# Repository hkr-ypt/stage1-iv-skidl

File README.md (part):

# Stage 1 I–V Characterization System — SKiDL Project

A complete, **executable** [SKiDL](https://github.com/devbisme/skidl) source
design for a Stage 1 I–V characterization instrument: a precision bipolar
**±10 V** voltage-source with 4-wire **Kelvin** sensing, **bipolar voltage and
current measurement over the whole sweep** (±11.8 V, ±97.8 mA guaranteed at the
nominal channel gain; ±11.76 V, ±97.3 mA with gain and offset at their limits; for a
source that can reach ±10.04 V and ±91.3 mA), hardware current limiting
(~49 mA), defense-in-depth protection, and a **shared 2.500 V reference** for
ratiometric measurement.

This project is the source of truth for the electrical design **and** the
board. Running it produces a **KiCad netlist** (`stage1_iv.net`), a
**hierarchical KiCad schematic** (`stage1_iv.kicad_sch` + one child
`.kicad_sch` per block, generated from the same in-memory circuit — see
[`SCHEMATIC.md`](SCHEMATIC.md)), the **placed and fully routed bipolar board**
(`stage1_iv.kicad_pcb`), plus a generated component manifest.

> **The board is generated from source and fully routed.** Its placement and
> copper are the human-routed board's (`unipolar-routed/`), captured into
> [`layout/stage1_iv.layout`](layout/stage1_iv.layout); the bipolar
> measurement change is applied to it by
> [`layout/bipolar.eco`](layout/bipolar.eco), the final hardware audit
> corrections by [`layout/audit_corrections.eco`](layout/audit_corrections.eco),
> the remaining corrections (FORCE+ photorelay, dead-rail clamps, FORCE−
> PTC, R10, F1 placement, mounting holes) by
> [`layout/final_corrections.eco`](layout/final_corrections.eco), and the
> re-routing to the repository clearances by
> [`layout/policy_clearance.eco`](layout/policy_clearance.eco): lists of
> add/remove operations, each with its reason. See
> [`docs/physical_design.md`](docs/physical_design.md),
> [`docs/audit_corrections.md`](docs/audit_corrections.md) and
> [`docs/final_corrections.md`](docs/final_corrections.md).
>
> **KiCad 10 DRC** (zones refilled, schematic parity on): 0 unconnected, 0
> parity problems, and **0 errors** both under the rules the board was routed
> to (its 0.20 mm netclass plus the scoped intra-footprint rules, every check
> on) and under the repository's stricter netclass policy (0.25–0.30 mm
> around sense and ±15 V nets). Two silkscreen-to-edge warnings at J3 are
> also on the original.
>
> **`unipolar-routed/` is the original, unipolar, human-routed reference** and is never
> modified. `python3 tools/reproduce_reference.py` proves the layout source
> regenerates it (identical copper, placement and connectivity; identical
> KiCad DRC and zone fill).

---

## Where the pin numbers come from

Every component is a **SKiDL-native part** (`tool=SKIDL`) declared in
[`libraries/custom_symbols.py`](libraries/custom_symbols.py), so the design runs
ERC, builds the netlist and validates connectivity as plain Python. But the
pins are **not written there**: each factory names an official KiCad `lib_id`,
and the pin numbers, pin names and electrical types are *read out of the
installed KiCad symbol library at build time* by
[`tools/resolve_kicad_libs.py`](tools/resolve_kicad_libs.py).

That is the whole point. A pin number in this repository cannot be stale,
invented, or remembered — it is whatever the symbol file on disk says, and
`tools/audit_identifiers.py` prints the file and line every value came from. A
`lib_id` that does not exist upstream stops the build instead of quietly
emitting a netlist that maps nets onto pads that are not there.

Each part still records, as component fields carried into the netlist:

- `KiCad_Lib` — the official KiCad library identifier the pins were read from
- `MPN` — manufacturer part number
- `Symbol_Source` — the symbol file and line the pins came from
- `Pins_Verified` — provenance of the pin **numbers** (see below)

**Connectivity is expressed exclusively by pin function name**
(`dac['VREF'] += VREF_2V5`), never by raw pin number. Where the official symbol
spells a pin differently from the design (`V_{REF}` vs `VREF`), an alias layer
keeps both spellings addressing the same pin; every alias is documented in
`ALIAS_DOCUMENTATION` and in
[`docs/identifier_resolution.md`](docs/identifier_resolution.md).

### Pin-number provenance

| Flag | Meaning | Parts |
|------|---------|-------|
| `RESOLVED` | Pin numbers read from an official KiCad symbol library, or from a project symbol authored from (or cross-checked pin by pin against) the manufacturer data sheet. Fabrication-safe. | every part |
| `VERIFY-DATASHEET` | Pin numbers read from a real, version-pinned library file that is **not** the manufacturer data sheet. Confirm before fabrication. | none (U5 was the last; resolved against TI SBOS070D and, for the fitted OPA547T, SBOS056F) |

`PLACEHOLDER-REMAP` no longer exists anywhere in this project;
[`validation/footprint_check.py`](validation/footprint_check.py) hard-fails if
it reappears.

Two parts have no symbol in the official KiCad libraries and live in the
project-local library [`libraries/stage1_iv.kicad_sym`](libraries/stage1_iv.kicad_sym),
generated by `tools/author_project_symbols.py` from committed provenance
excerpts under `libraries/provenance/`:

- **ADS1256** — authored from TI **SBAS288K** (rev. K, Sept 2013), "Terminal
  Functions" table, page 5. `RESOLVED`.
- **OPA548T** (the symbol of U5, which is fitted with an **OPA547T**: same
  family, pinout and package; `docs/final_audit.md`) — its symbol comes from
  a pinned commit of a published third-party KiCad library, and every pin is
  cross-checked against the TI **SBOS070D** "Pin Functions" table, committed
  verbatim as `libraries/provenance/opa548_sbos070d_pin_functions.txt`, and
  against the TI **SBOS056F** "Pin Configurations" drawing of the OPA547,
  `libraries/provenance/opa547_sbos056f_pin_configurations.txt`. The build
  stops on any disagreement. `RESOLVED`. Its footprint is a project copy of KiCad's
  staggered TO-220-7 with 1.2 mm drills (`stage1_iv.pretty`, generated by
  `tools/vendor_footprints.py`).

---

## Project structure

```
stage1-iv-skidl/
├── main.py                     # instantiate all blocks, validate, emit outputs
├── requirements.txt
├── manifest.yaml               # machine-readable design summary + unresolved items
├── README.md
├── SCHEMATIC.md                # how the .kicad_sch output is generated
│
├── blocks/
│   ├── nets.py                 # global cross-sheet nets (the net manifest)
│   ├── power.py                # Sheet 1 — power regulation & reference
│   ├── mcu.py                  # Sheet 2 — STM32F411 + USB/SWD/clock
│   ├── dac_sweep.py            # Sheet 3 — DAC8552 + OPA2277 level-shift
│   ├── output_buffer.py        # Sheet 4 — OPA547 power buffer
│   ├── current_sense.py        # Sheet 5 — shunt + INA128 current sense
│   ├── voltage_sense.py        # Sheet 6 — INA128 Kelvin voltage sense
│   ├── adc.py                  # Sheet 7 — ADS1256 + RC filters
│   └── protection.py           # Sheet 8 — fuse/TVS + DUT connector
│
├── generators/
│   ├── schematic.py            # hierarchical .kicad_sch emitter (live circuit)
│   ├── routed_pcb.py           # THE board: circuit + layout/ + ECOs -> .kicad_pcb
│   ├── layout.py               # layout source + ECO model (parse, apply, write)
│   ├── footprint_xform.py      # place a library footprint as KiCad stores it
│   └── pcb.py                  # footprint prep; bootstrap auto-placer (--autoplace)
│
├── layout/
│   ├── stage1_iv.layout        # placement + copper, captured from unipolar-routed/
│   ├── bipolar.eco             # the bipolar change: reasoned add/remove ops
│   ├── audit_corrections.eco   # the final hardware audit corrections (F1–F4, V1, …)
│   ├── final_corrections.eco   # U12/D7/R39, D8/D9, F2, R10, F1 move, H1–H3
│   └── policy_clearance.eco    # re-routing to the repository netclass clearances
│
├── tools/
│   ├── resolve_kicad_libs.py   # THE resolver: reads installed KiCad libraries
│   ├── install_kicad_libs.sh   # install a pinned upstream library revision
│   ├── audit_identifiers.py    # per-part identifier / pad audit -> markdown
│   ├── author_project_symbols.py # generate libraries/stage1_iv.kicad_sym
│   ├── kicad_roundtrip.py      # verify the schematic through kicad-cli
│   ├── check_kicad_loads.py    # KiCad itself reads the library/schematic/board
│   ├── gen_project_config.py   # lib tables + board setup from netclasses
│   ├── vendor_footprints.py    # pin the used footprints into the repository
│   ├── measure_pad_gaps.py     # measure intrinsic pad gaps from the footprints
│   ├── compare_routed_board.py # unipolar-routed/ board vs the SKiDL design (ECO list)
│   ├── capture_layout.py       # routed board -> layout source (--check)
│   ├── reproduce_reference.py  # prove the layout regenerates unipolar-routed/
│   ├── compare_boards.py       # semantic board-vs-board comparison
│   ├── board_geometry.py       # real-copper geometry (shapely)
│   ├── eco_route.py            # design an ECO track against real copper
│   └── test_guard_fails.sh     # fault-injection: prove the guard fails
│
├── validation/
│   ├── erc.py                  # SKiDL ERC + structural checks
│   ├── assertions.py           # custom connectivity/topology assertions
│   ├── footprint_check.py      # identifiers/pads guard (aborts the build)
│   ├── routed_board_check.py   # board of record: source, parity, KiCad DRC
│   ├── drc_check.py            # board checks (shared; auto-placed board)
│   ├── measurement_range.py    # every reachable V/I point fits the ADC, signed
│   └── schematic_check.py      # schematic <-> netlist consistency validator
│
├── docs/
│   ├── final_audit.md                # final design audit: findings, changes, evidence
│   ├── changes_since_bipolar.md      # every change since the bipolar design (bfbb140)
│   ├── final_corrections.md          # remaining hardware corrections: analysis, validation
│   ├── audit_corrections.md          # final hardware audit: what changed, validation record
│   ├── firmware_handoff.md           # what the hardware requires of the firmware
│   ├── bringup_checklist.md          # assembly + first-power procedure
│   ├── bipolar_measurement.md        # bipolar V/I design + routed-board ECO
│   ├── physical_design.md            # layout source, ECO, reproduction, DRC
│   ├── identifier_resolution.md      # what was wrong, what it became, sources
│   ├── FAB_CONSTRAINTS.md            # assumed fabricator capability (F1..F12)
│   ├── pcb_generation.md             # netclasses, rules, the auto-placer
│   ├── audit_identifiers_before.md   # pre-fix baseline
│   └── audit_identifiers_after.md    # identifier audit of the current design (generated)
│
├── unipolar-routed/            # ORIGINAL unipolar human-routed KiCad project:
│                               # the reference, never modified (its README.md)
├── kicad_libs.json             # explicit KiCad library locations (optional)
├── sym-lib-table               # registers libraries/stage1_iv.kicad_sym
│
└── libraries/
    ├── custom_symbols.py       # part factories; pins READ from the libraries
    ├── netclasses.py           # netclasses; every value cites FAB_CONSTRAINTS
    ├── stage1_iv.kicad_sym     # generated: parts with no upstream symbol
    └── provenance/             # verbatim sources every project pin came from
```

Each block exposes a `create_*_block(nets)` function that instantiates its parts
and connects them to the shared global nets. `main.py` builds all eight sheets.

---

## Install & run

```bash
# 1. SKiDL and its import-time dependencies. The optional PCB-placement extras
#    (kinet2pcb, hierplace) are not needed and may fail to build, so skip them.
pip install --no-deps skidl==2.2.3
pip install graphviz future simp_sexp rich ply pyyaml
#    kinparse's setup.py predates modern setuptools:
SETUPTOOLS_USE_DISTUTILS=stdlib pip install --no-build-isolation kinparse

# 2. Check what KiCad libraries this machine has, if any. ALWAYS START HERE:
#    a partially-copied symbols directory looks like a working install until
#    ERC reports a hundred "library not found" errors.
python3 tools/kicad_env.py --check --diagnose
#      exit 0 = complete, 2 = none found, 3 = INCOMPLETE (and it names what is
#      missing). KiCad is OPTIONAL — see "Building without KiCad" below.

# 3. Optional: install exactly the pinned library revision this design was
#    resolved against (see docs/LIBRARY_DEPENDENCIES.md).
tools/install_kicad_libs.sh "$HOME/.local/share/kicad" 9.0.9.1
export KICAD9_SYMBOL_DIR="$HOME/.local/share/kicad/symbols"
export KICAD9_FOOTPRINT_DIR="$HOME/.local/share/kicad/footprints"
#    or write your paths into kicad_paths.local.json (gitignored).

# Build: validate + emit netlist + schematic + manifests
python3 main.py

# Just emit the netlist
python3 main.py --netlist-only

# Just emit the hierarchical schematic
python3 main.py --schematic-only

# Verify schematic <-> netlist consistency (exits non-zero on mismatch)
python3 validation/schematic_check.py

# Structural guard: identifiers resolve, pins map to pads, no undeclared
# floating pads, no placeholder provenance (also run from main.py)
python3 validation/footprint_check.py

# ERC gate standalone: hard-fails on any error, any un-allow-listed warning,
# or any PWR_FLAG invariant violation
python3 validation/erc.py

# KiCad's power-driver ERC rules, evaluated on the emitted .kicad_sch files
python3 tools/kicad_erc_power.py

# Audit every part against the installed libraries
python3 tools/audit_identifiers.py > docs/audit_identifiers_after.md

# Verify the emitted schematic through KiCad's own parser
python3 tools/kicad_roundtrip.py

# Prove the guard fails when a bad identifier is reintroduced
tools/test_guard_fails.sh

# Regenerated files are current (project symbol library, lib tables, deps doc)
python3 tools/author_project_symbols.py --check
python3 tools/gen_project_config.py --check

# No committed file contains a machine-specific absolute path
python3 tools/check_no_abs_paths.py
```

### Building without KiCad

`python3 main.py` runs with no KiCad installed: pin data falls back to the
committed project symbol library `libraries/stage1_iv.kicad_sym`. The build then
reports **SKIPPED** for every KiCad-conformance check and never anything
resembling a pass:

```
  KiCad libraries ....... NOT FOUND
  Symbol resolution ..... SKIPPED (no KiCad libraries to check against)
  Footprint resolution .. SKIPPED (no KiCad libraries to check against)
  SKiDL ERC ............. 0 errors, 0 warnings
  KiCad ERC ............. NOT RUN
```

### Opening in KiCad

`stage1_iv.kicad_pro`, `sym-lib-table` and `fp-lib-table` are committed and
contain **no absolute paths** — only `${KIPRJMOD}` and KiCad's own
`${KICAD9_SYMBOL_DIR}` / `${KICAD9_FOOTPRINT_DIR}`. Open `stage1_iv.kicad_pro`
and every symbol resolves from `libraries/stage1_iv.kicad_sym` inside the
repository, so the schematic opens correctly even on a machine whose stock
libraries are missing or incomplete.

**Update the PCB with "Update PCB from Schematic", never by importing
`stage1_iv.net`** — the schematic is the single source of truth for KiCad and
the netlist is intentionally flat. See
[`docs/library_strategy.md`](docs/library_strategy.md) §4 for the decision and
its consequences for an existing board.

Expected result: **0 SKiDL ERC errors, 0 SKiDL ERC warnings, 15/15 assertions
PASS, measurement-range check PASS, 0 unresolved identifiers, 0 unaccounted pads**, and:

> **SKiDL ERC is not KiCad ERC.** They are different checks with different
> coverage — see [Validation](#validation) below for exactly what each one does
> and does not cover. A clean SKiDL ERC run is evidence about the SKiDL
> circuit; it says nothing about the KiCad ERC dialog.

- `stage1_iv.net` — KiCad netlist
- `stage1_iv.kicad_sch` + 8 child `.kicad_sch` — hierarchical KiCad schematic
  (self-contained; see below and [`SCHEMATIC.md`](SCHEMATIC.md))
- `stage1_iv.kicad_pcb` — the bipolar board, placed and **fully routed**
  (KiCad 9/10 schema, **opens in KiCad 10**; zones are stored unfilled — press
  B, or plot with `--check-zones`). Generated from the circuit,
  `layout/stage1_iv.layout` and the four ECOs in `layout/`; checked by
  `validation/routed_board_check.py` (see
  [`docs/physical_design.md`](docs/physical_design.md)). Opening it and
  pressing *Update PCB from Schematic* changes **nothing** — that is a checked
  property, not a hope (`validation/update_pcb_noop.py`)
- `component_manifest.md` — generated component table

> SKiDL prints benign `KICADn_SYMBOL_DIR` / `fp-lib-table` warnings on import
> and one internal no-connect "Missing tag" notice during netlist generation.
> These come from SKiDL's own library loader, which this project does not use
> (it reads the libraries through `tools/resolve_kicad_libs.py`), and do not
> affect the design.

---

## Generation stages (as required by the spec)

1. **Manifest & library identification** — every component, its intended KiCad
   library, and every unresolved/placeholder symbol are enumerated in
   `manifest.yaml` and regenerated into `component_manifest.md`.
2. **Individual SKiDL blocks** — `blocks/*.py`, one per hierarchical sheet.
3. **Integration** — `main.py` wires blocks through `blocks/nets.py`.
4. **ERC + connectivity validation** — `validation/erc.py` and
   `validation/assertions.py`.
5. **Final project files** — this repository.

## Validation

**ERC (`validation/erc.py`)** — and the first thing to know is that **SKiDL ERC
and KiCad ERC are different checks with different coverage. A pass here is not
evidence about KiCad ERC.**

SKiDL's ERC covers: pins connected to nothing; pins on the no-connect net that
also carry a real net; nets with fewer than two pins; pin-type conflicts; and
insufficient drive — a net whose maximum pin drive is below what some pin on it
requires. That last one is SKiDL's analogue of KiCad's `power_pin_not_driven`,
and the `PWR_FLAG` parts on the eight externally-sourced rails satisfy both.

SKiDL's ERC does **not** cover, and KiCad's does: symbol and library resolution
(`lib_symbol_issues`, `lib_symbol_mismatch`, "symbol not found in library");
footprint link resolution (`footprint_link_issues`); and everything geometric —
wire/label/pin overlap, dangling wire ends, bus definition errors, sheet-pin
mismatch. The first two are covered instead by
[`validation/footprint_check.py`](validation/footprint_check.py) and
[`tools/audit_identifiers.py`](tools/audit_identifiers.py); the geometric rules
are not checked anywhere in this repository.

The gate is real: `run_erc` reads `skidl.erc_logger`'s counters around the
`ERC()` call, cross-checks them against the captured message texts, and
**raises** on any error, on any warning not in an explicitly justified
allow-list (currently empty), and on any violation of the `PWR_FLAG` invariant.
`main.py` prints the actual counts and exits non-zero. Current result:
**0 errors, 0 warnings**.

**Power flags.** Eight rails have no on-board driver because their energy comes
from outside the board, and each carries one `power:PWR_FLAG` instantiated at
its physical point of entry:

| Net | Physical source | Flag | Attached in |
|---|---|---|---|
| `+15VA` | bench supply, J1 pin 1 | `#FLG1` | `blocks/power.py` |
| `-15VA` | bench supply, J1 pin 2 | `#FLG2` | `blocks/power.py` |
| `+5V_RAW` | bench supply, J1 pin 3 | `#FLG3` | `blocks/power.py` |
| `DGND` | bench supply return, J1 pin 4 | `#FLG4` | `blocks/power.py` |
| `+5VA` | `+5V_RAW` through ferrite bead FB1 | `#FLG5` | `blocks/power.py` |
| `AGND` | analog return; separate net from DGND (R31 star) | `#FLG6` | `blocks/power.py` |
| `VBUS` | USB host, through J3 | `#FLG7` | `blocks/mcu.py` |
| `VDDA` | `+3V3D` through ferrite bead FB2 | `#FLG8` | `blocks/mcu.py` |

`+3V3D` and `VREF_2V5` are deliberately **not** flagged: U1.VOUT and U2.Vout
genuinely drive them, and a flag there would mask a future regulator wiring
error. `validation/erc.py::check_power_flags` enforces all of this — a missing
flag, a flag on an undeclared net, and a flag on a net that already has a real
driver are each a hard failure.

**Structural guard (`validation/footprint_check.py`)** — wired into `main.py`,
so the build **aborts** on any failure. Five hard checks:

1. every `KiCad_Lib` resolves to a real library **and** symbol
2. every footprint resolves to a real library **and** footprint
3. every declared pin number is a real pad name (a pin with no pad silently
   drops its net on the PCB)
4. every pad is either netted or an explicit no-connect listed in
   `UNCONNECTED_PAD_ALLOWLIST` with a written reason
5. no part carries `Pins_Verified == "PLACEHOLDER-REMAP"`

Current result: 141 parts (9 virtual PWR_FLAGs), 406 pads, **359 netted, 47
declared no-connect, 0 unaccounted**. `tools/test_guard_fails.sh` reintroduces real defects one
at a time (43 cases, among them the five structural ones above and, since the
audit corrections, the midpoint back on VREF_2V5, the DAC reference wired
around U11, a DC path onto DAC_ARM and R30 back to 1/4 W) and confirms every
one is caught. `python3 validation/assertions.py` runs the connectivity
assertions on their own.

**Custom assertions (`validation/assertions.py`)** — all **15 PASS**:

- ADC reference (`U8.VREFP`) is on `VREF_2V5`, and the DAC reference
  (`U4.VREF`) reaches it only through the U11 gate (never directly)
- the sweep midpoint divider is fed from DAC channel B (`VOUTB`), not from a
  fixed reference
- the DAC reference gate: U11 between `VREF_2V5` and `U4.VREF`, a pull-down on
  the DAC side, SEL on `DAC_ARM`
- `DAC_ARM` has no DC path from any rail or GPIO: it is driven only through
  the charge-pump diode from a capacitively coupled heartbeat
- the DAC's `/SYNC` (CS_DAC) has a pull-up
- FORCE+ path = `power amp (U5) → R9 → F1(fuse) → R30 → U12 (photorelay) → D5(TVS) → J4`
- Kelvin sense (`SENSE±`) is independent from the force path
- ADC uses **SPI2**, DAC uses **SPI1**
- SPI1 and SPI2 are physically **separate buses**
- AGND and DGND join **only** at the `R31` star point
- every required manifest net exists and is populated
- **USB-C (J3): all four GND pads on DGND, all four VBUS pads on VBUS, both
  D+ pads tied and both D- pads tied** (the receptacle is symmetric — wiring
  one of each pair gives a port that works in one cable orientation only)
- **the measurement zero**: `U6.REF`, `U7.REF` and the ADC's `AINCOM` are all
  on `VREF_2V5` (none left on AGND)
- **the Kelvin attenuator**: each U7 input is fed by one series resistor from
  its SENSE jack and one shunt resistor to AGND, with nothing across the inputs

**Measurement range (`validation/measurement_range.py`)** — from the part
values in the live circuit: the sweep span, the largest current any passive DUT
can draw (`V_SWEEP/(R30 + R10)`, independent of U5's current limit), both
channels' transfer functions, and the voltage on each ADS1256 input at those
extremes with worst-case tolerances. Fails the build if any normal operating
point leaves the ADC's absolute input window (`AGND − 0.1 … AVDD + 0.1 V`) or
its PGA = 2 full scale. It also bounds the FORCE-path fault (U5 driven into a
15.5 V rail, every series part at its guaranteed minimum: 128 mA into a DUT
short, 143 mA with FORCE+ on AGND) and an external source on J7 (F2 + R10:
1.19 A), and checks R9, R30 and R10 against their ratings. Current result:
worst-case headroom 334 mV (V) and 115 mV (I); fault dissipation R30 1.96 W
of 2 W, R9 0.21 W of 0.5 W, R10 0.16 W of 3 W and 14.3 W of its 15 W
short-time rating ([`docs/final_corrections.md`](docs/final_corrections.md)
§2.7).

**Identifier audit (`tools/audit_identifiers.py`)** — per part, whether the
symbol and footprint resolve, symbol pins vs footprint pads, unaccounted pads,
and the file:line every value was read from. Before/after snapshots:
[`docs/audit_identifiers_before.md`](docs/audit_identifiers_before.md),
[`docs/audit_identifiers_after.md`](docs/audit_identifiers_after.md); the full
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
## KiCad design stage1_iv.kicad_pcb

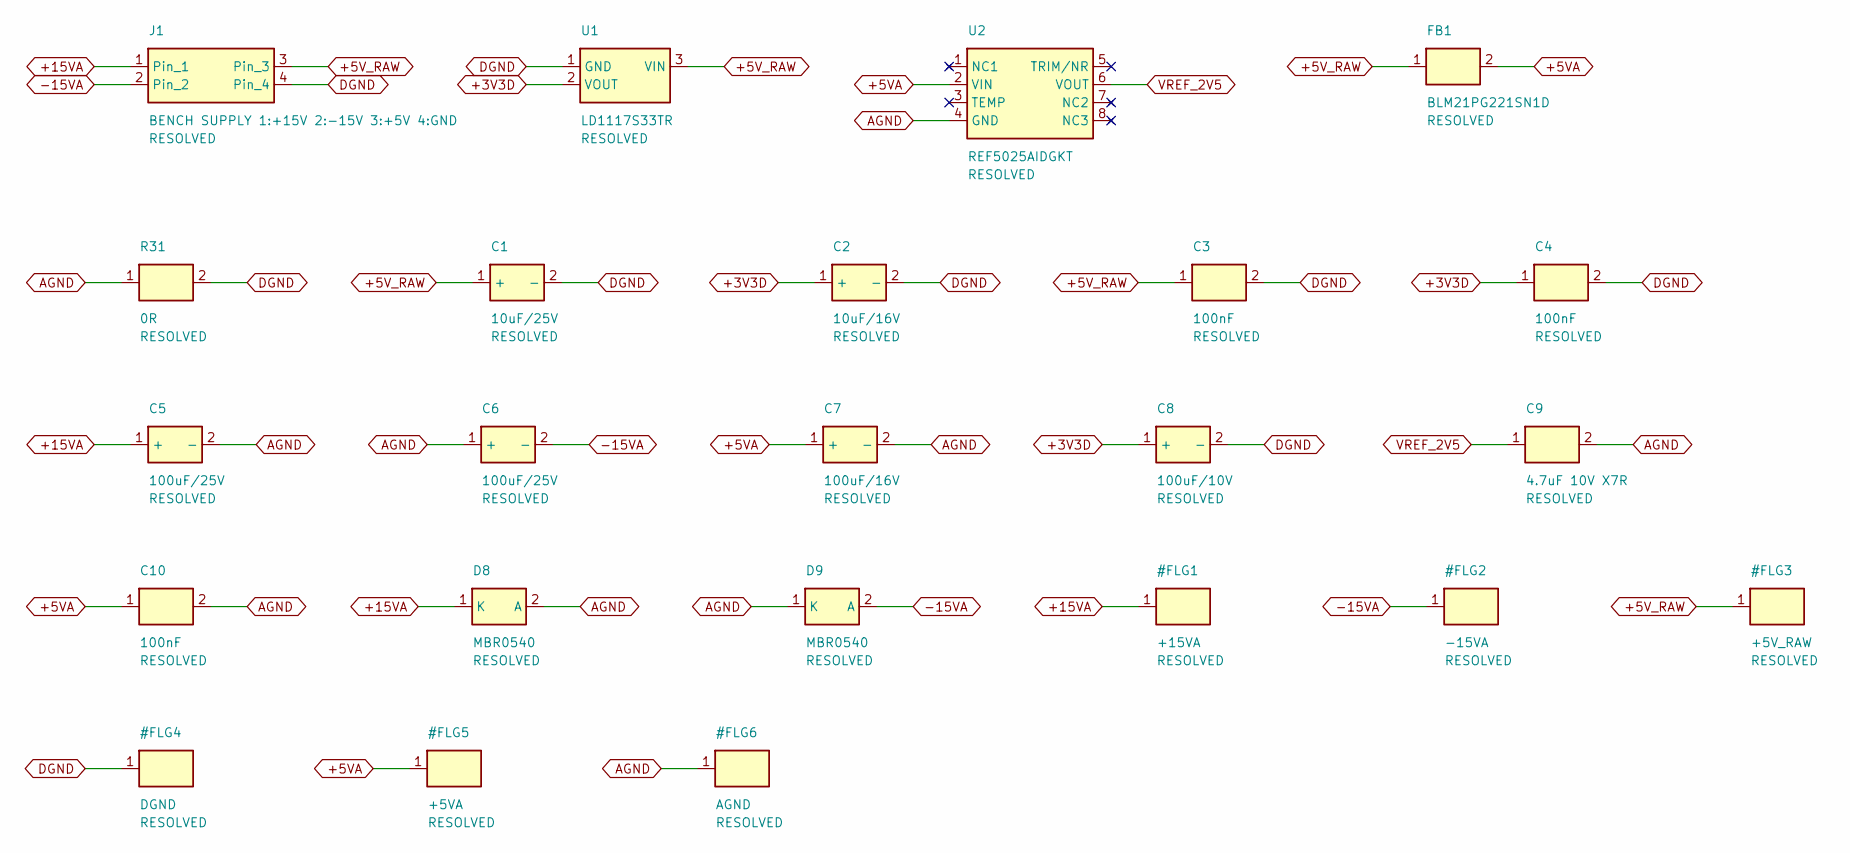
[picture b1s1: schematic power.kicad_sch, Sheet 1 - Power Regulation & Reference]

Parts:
C1: 10uF/25V; CP_EIA-3528-21_Kemet-B; MPN generic
C2: 10uF/16V; CP_EIA-3528-21_Kemet-B; MPN generic
C3, C4: 100nF; C_0805_2012Metric; MPN generic
C5, C6: 100uF/25V; CP_Elec_8x10.5; MPN generic
C7: 100uF/16V; CP_Elec_6.3x7.7; MPN generic
C8: 100uF/10V; CP_Elec_6.3x5.4; MPN generic
C9: 4.7uF 10V X7R; C_0603_1608Metric; MPN generic
C10: 100nF; C_0603_1608Metric; MPN generic
D8, D9: MBR0540; D_SOD-123; MPN MBR0540
FB1: BLM21PG221SN1D; L_0805_2012Metric; MPN BLM21PG221SN1D
J1: BENCH SUPPLY 1:+15V 2:-15V 3:+5V 4:GND; TerminalBlock_Phoenix_MKDS-1,5-4-5.08_1x04_P5.08mm_Horizont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; MPN MKDS 1,5/4-5,08
R31: 0R; R_0805_2012Metric; MPN generic
U1: LD1117S33TR; SOT-223-3_TabPin2; MPN LD1117S33TR
U2: REF5025AIDGKT; VSSOP-8_3x3mm_P0.65mm; MPN REF5025AIDGKT

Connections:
+3V3D: C2.1 (+), C4.1, C8.1 (+), U1.2 (VOUT); also elsewhere on the board
+5VA: C7.1 (+), C10.1, FB1.2, U2.2 (VIN); also elsewhere on the board
+5V_RAW: C1.1 (+), C3.1, FB1.1, J1.3, U1.3 (VIN)
+15VA: C5.1 (+), D8.1 (K), J1.1; also elsewhere on the board
-15VA: C6.2 (-), D9.2 (A), J1.2; also elsewhere on the board
AGND: C5.2 (-), C6.1 (+), C7.2 (-), C9.2, C10.2, D8.2 (A), D9.1 (K), R31.1, U2.4 (GND); also elsewhere on the board
DGND: C1.2 (-), C2.2 (-), C3.2, C4.2, C8.2 (-), J1.4, R31.2, U1.1 (GND); also elsewhere on the board
VREF_2V5: C9.1, U2.6 (VOUT); also elsewhere on the board

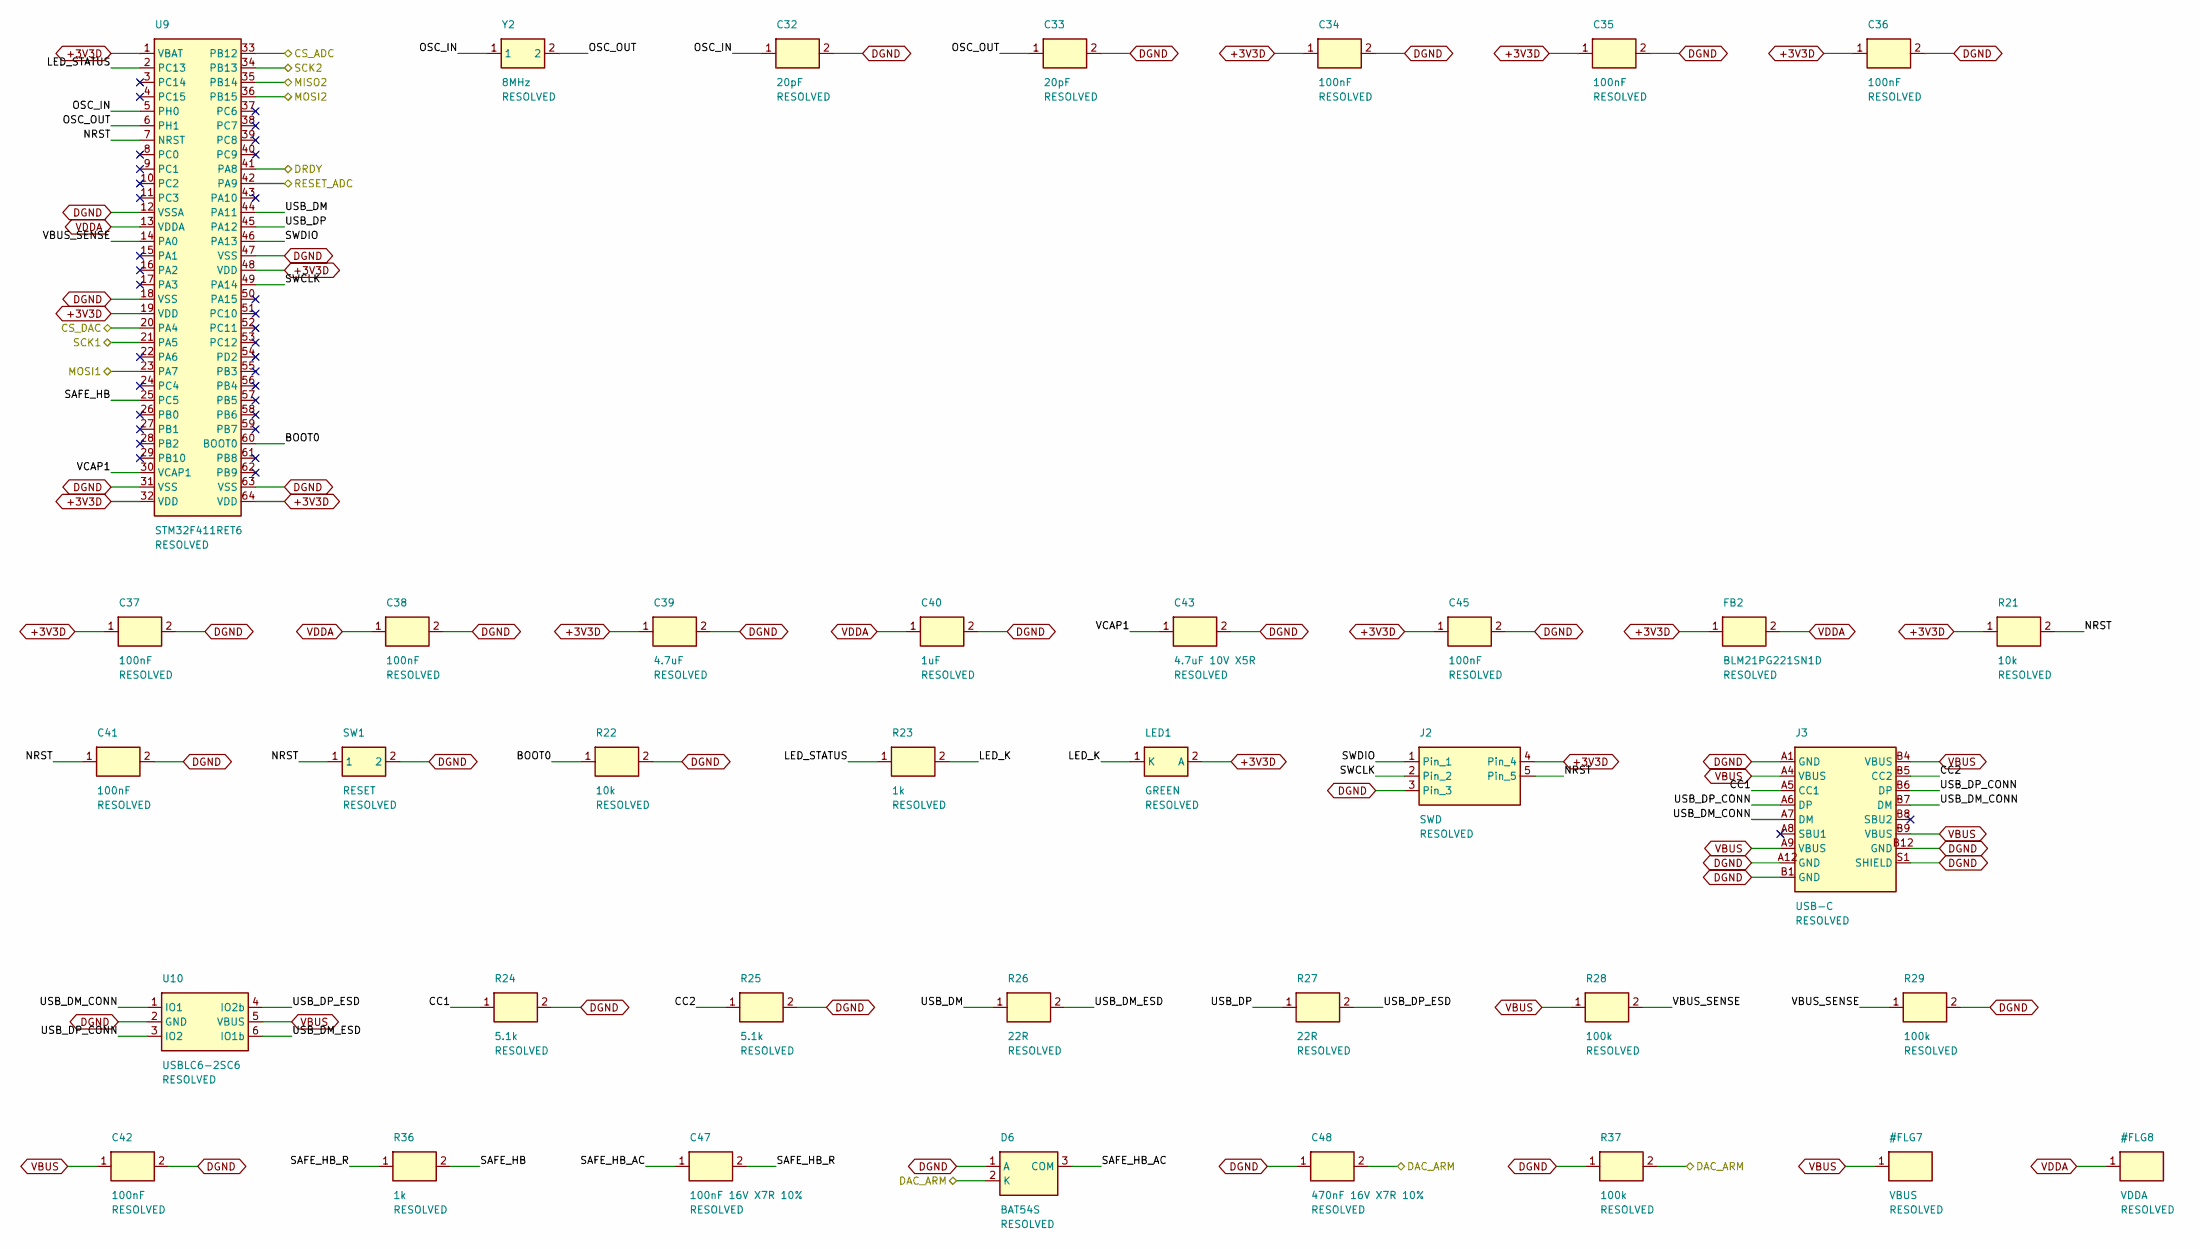
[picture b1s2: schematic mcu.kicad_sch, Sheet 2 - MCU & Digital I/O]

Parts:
C32, C33: 20pF; C_0603_1608Metric; MPN generic
C34, C35, C36, C37, C38, C41, C42, C45: 100nF; C_0603_1608Metric; MPN generic
C39: 4.7uF; C_0805_2012Metric; MPN generic
C40: 1uF; C_0603_1608Metric; MPN generic
C43: 4.7uF 10V X5R; C_0603_1608Metric; MPN generic
C47: 100nF 16V X7R 10%; C_0603_1608Metric; MPN generic
C48: 470nF 16V X7R 10%; C_0603_1608Metric; MPN generic
D6: BAT54S; SOT-23; MPN BAT54S
FB2: BLM21PG221SN1D; L_0805_2012Metric; MPN BLM21PG221SN1D
J2: SWD; PinHeader_1x05_P2.54mm_Vertical; MPN generic-2.54mm
J3: USB-C; USB_C_Receptacle_GCT_USB4085; MPN GCT USB4085
LED1: GREEN; LED_0805_2012Metric; MPN generic
R21, R22: 10k; R_0603_1608Metric; MPN generic
R23, R36: 1k; R_0603_1608Metric; MPN generic
R24, R25: 5.1k; R_0603_1608Metric; MPN generic
R26, R27: 22R; R_0603_1608Metric; MPN generic
R28, R29, R37: 100k; R_0603_1608Metric; MPN generic
SW1: RESET; SW_PUSH_6mm; MPN generic
U9: STM32F411RET6; LQFP-64_10x10mm_P0.5mm; MPN STM32F411RET6
U10: USBLC6-2SC6; SOT-23-6; MPN USBLC6-2SC6
Y2: 8MHz; Crystal_SMD_HC49-SD; MPN generic

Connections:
+3V3D: C34.1, C35.1, C36.1, C37.1, C39.1, C45.1, FB2.1, J2.4, LED1.2 (A), R21.1, U9.1 (VBAT), U9.19 (VDD), U9.32 (VDD), U9.48 (VDD), U9.64 (VDD); also elsewhere on the board
/CS_ADC: U9.33 (PB12); also elsewhere on the board
/CS_DAC: U9.20 (PA4); also elsewhere on the board
/DAC_ARM: C48.2, D6.2 (K), R37.2; also elsewhere on the board
/DRDY: U9.41 (PA8); also elsewhere on the board
/MISO2: U9.35 (PB14); also elsewhere on the board
/MOSI1: U9.23 (PA7); also elsewhere on the board
/MOSI2: U9.36 (PB15); also elsewhere on the board
/RESET_ADC: U9.42 (PA9); also elsewhere on the board
/SCK1: U9.21 (PA5); also elsewhere on the board
/SCK2: U9.34 (PB13); also elsewhere on the board
/mcu/BOOT0: R22.1, U9.60 (BOOT0)
/mcu/CC1: J3.A5 (CC1), R24.1
/mcu/CC2: J3.B5 (CC2), R25.1
/mcu/LED_K: LED1.1 (K), R23.2
/mcu/LED_STATUS: R23.1, U9.2 (PC13)
/mcu/NRST: C41.1, J2.5, R21.2, SW1.1, U9.7 (NRST)
/mcu/OSC_IN: C32.1, U9.5 (PH0), Y2.1
/mcu/OSC_OUT: C33.1, U9.6 (PH1), Y2.2
/mcu/SAFE_HB: R36.2, U9.25 (PC5)
/mcu/SAFE_HB_AC: C47.1, D6.3 (COM)
/mcu/SAFE_HB_R: C47.2, R36.1
/mcu/SWCLK: J2.2, U9.49 (PA14)
/mcu/SWDIO: J2.1, U9.46 (PA13)
/mcu/USB_DM: R26.1, U9.44 (PA11)
/mcu/USB_DM_CONN: J3.A7 (DM), J3.B7 (DM), U10.1 (IO1)
/mcu/USB_DM_ESD: R26.2, U10.6 (IO1b)
/mcu/USB_DP: R27.1, U9.45 (PA12)
/mcu/USB_DP_CONN: J3.A6 (DP), J3.B6 (DP), U10.3 (IO2)
/mcu/USB_DP_ESD: R27.2, U10.4 (IO2b)
/mcu/VBUS_SENSE: R28.2, R29.1, U9.14 (PA0)
/mcu/VCAP1: C43.1, U9.30 (VCAP1)
DGND: C32.2, C33.2, C34.2, C35.2, C36.2, C37.2, C38.2, C39.2, C40.2, C41.2, C42.2, C43.2, C45.2, C48.1, D6.1 (A), J2.3, J3.A1 (GND), J3.A12 (GND), J3.B1 (GND), J3.B12 (GND), J3.S1 (SHIELD), R22.2, R24.2, R25.2, R29.2, R37.1, SW1.2, U9.12 (VSSA), U9.18 (VSS), U9.31 (VSS), U9.47 (VSS), U9.63 (VSS), U10.2 (GND); also elsewhere on the board
VBUS: C42.1, J3.A4 (VBUS), J3.A9 (VBUS), J3.B4 (VBUS), J3.B9 (VBUS), R28.1, U10.5 (VBUS)
VDDA: C38.1, C40.1, FB2.2, U9.13 (VDDA)

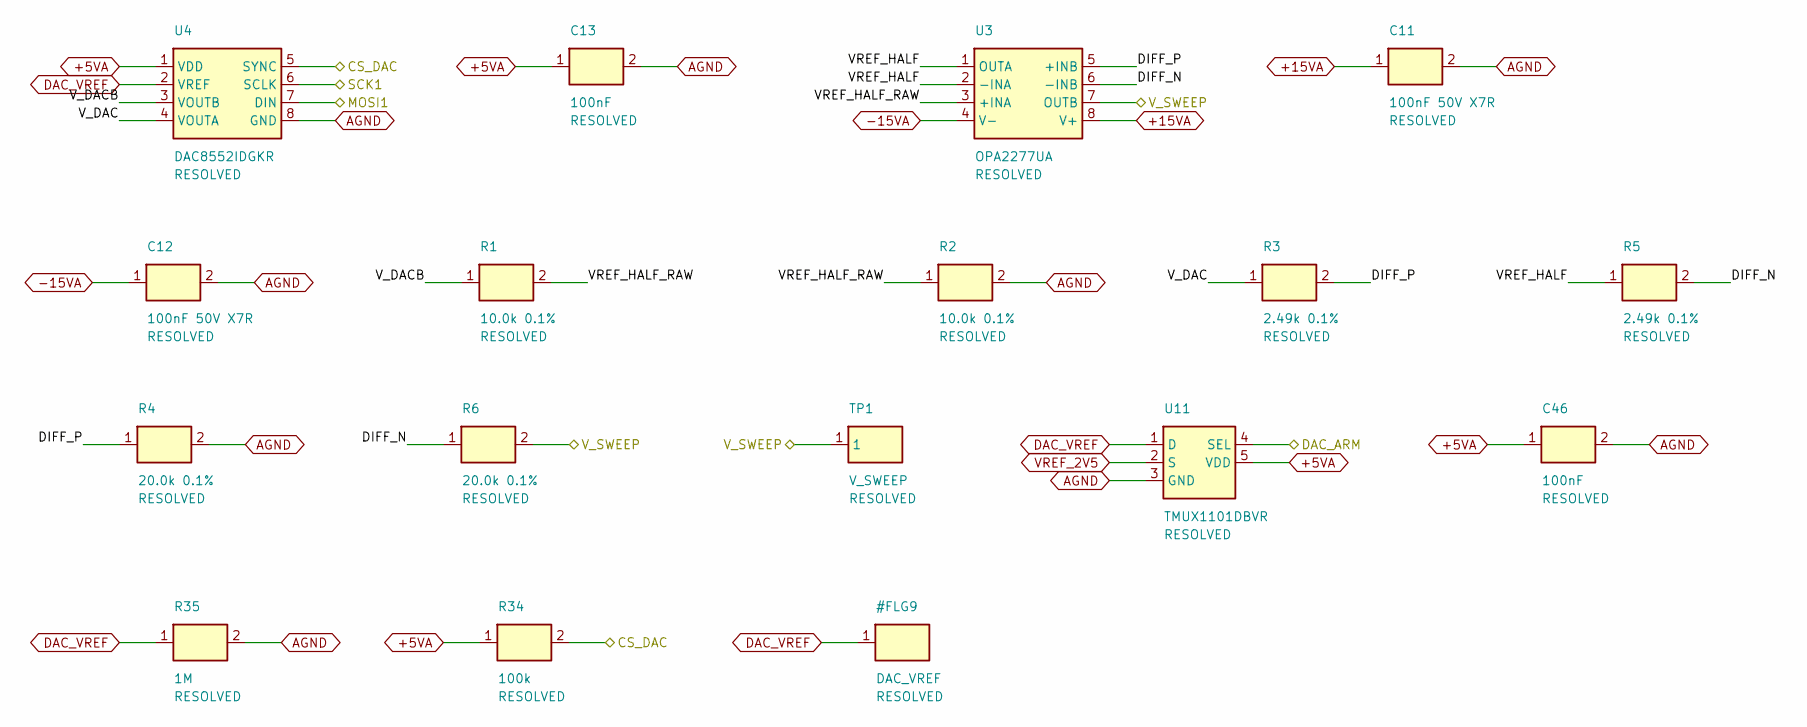
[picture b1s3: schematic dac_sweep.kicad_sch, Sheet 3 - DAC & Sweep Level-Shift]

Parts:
C11, C12: 100nF 50V X7R; C_0603_1608Metric; MPN generic
C13, C46: 100nF; C_0603_1608Metric; MPN generic
R1, R2: 10.0k 0.1%; R_0603_1608Metric; MPN generic
R3, R5: 2.49k 0.1%; R_0603_1608Metric; MPN generic
R4, R6: 20.0k 0.1%; R_0603_1608Metric; MPN generic
R34: 100k; R_0603_1608Metric; MPN generic
R35: 1M; R_0603_1608Metric; MPN generic
TP1: V_SWEEP; TestPoint_Pad_D1.5mm; MPN n/a
U3: OPA2277UA; SOIC-8_3.9x4.9mm_P1.27mm; MPN OPA2277UA
U4: DAC8552IDGKR; VSSOP-8_3x3mm_P0.65mm; MPN DAC8552IDGKR
U11: TMUX1101DBVR; SOT-23-5; MPN TMUX1101DBVR

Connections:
+5VA: C13.1, C46.1, R34.1, U4.1 (VDD), U11.5 (VDD); also elsewhere on the board
+15VA: C11.1, U3.8 (V+); also elsewhere on the board
-15VA: C12.1, U3.4 (V-); also elsewhere on the board
/CS_DAC: R34.2, U4.5 (SYNC); also elsewhere on the board
/DAC_ARM: U11.4 (SEL); also elsewhere on the board
/MOSI1: U4.7 (DIN); also elsewhere on the board
/SCK1: U4.6 (SCLK); also elsewhere on the board
/V_SWEEP: R6.2, TP1.1, U3.7 (OUTB); also elsewhere on the board
/dac_sweep/DIFF_N: R5.2, R6.1, U3.6 (-INB)
/dac_sweep/DIFF_P: R3.2, R4.1, U3.5 (+INB)
/dac_sweep/VREF_HALF: R5.1, U3.1 (OUTA), U3.2 (-INA)
/dac_sweep/VREF_HALF_RAW: R1.2, R2.1, U3.3 (+INA)
/dac_sweep/V_DAC: R3.1, U4.4 (VOUTA)
/dac_sweep/V_DACB: R1.1, U4.3 (VOUTB)
AGND: C11.2, C12.2, C13.2, C46.2, R2.2, R4.2, R35.2, U4.8 (GND), U11.3 (GND); also elsewhere on the board
DAC_VREF: R35.1, U4.2 (VREF), U11.1 (D)
VREF_2V5: U11.2 (S); also elsewhere on the board

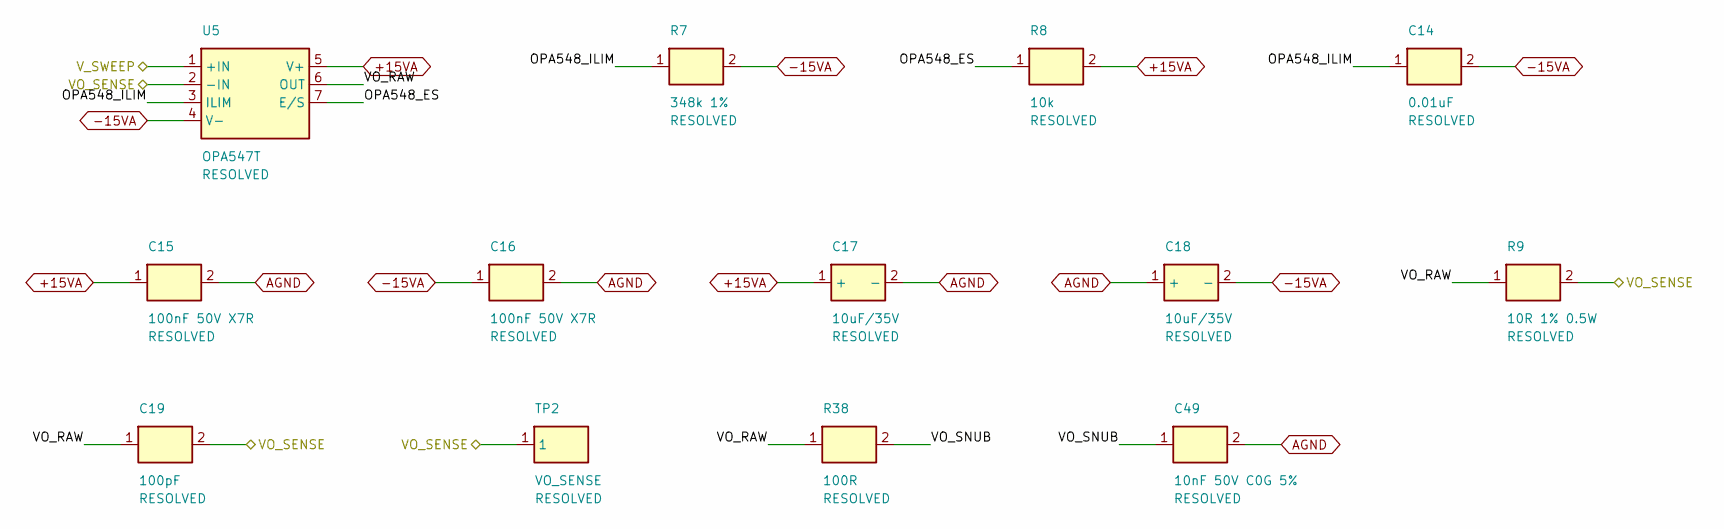
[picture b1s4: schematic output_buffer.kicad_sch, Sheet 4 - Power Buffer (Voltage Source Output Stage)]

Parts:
C14: 0.01uF; C_0805_2012Metric; MPN generic
C15, C16: 100nF 50V X7R; C_0805_2012Metric; MPN generic
C17, C18: 10uF/35V; CP_EIA-3528-21_Kemet-B; MPN TCJB106M035R0200E
C19: 100pF; C_0603_1608Metric; MPN generic
C49: 10nF 50V C0G 5%; C_0805_2012Metric; MPN generic
R7: 348k 1%; R_1206_3216Metric; MPN generic
R8: 10k; R_0603_1608Metric; MPN generic
R9: 10R 1% 0.5W; R_1206_3216Metric; MPN generic
R38: 100R; R_0805_2012Metric; MPN generic
TP2: VO_SENSE; TestPoint_Pad_D1.5mm; MPN n/a
U5: OPA547T; TO-220-7_P2.54x3.7mm_StaggerOdd_Lead3.8mm_Vertical_Drill1.2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; MPN OPA547T

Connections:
+15VA: C15.1, C17.1 (+), R8.2, U5.5 (V+); also elsewhere on the board
-15VA: C14.2, C16.1, C18.2 (-), R7.2, U5.4 (V-); also elsewhere on the board
/VO_SENSE: C19.2, R9.2, TP2.1, U5.2 (-IN); also elsewhere on the board
/V_SWEEP: U5.1 (+IN); also elsewhere on the board
/output_buffer/OPA548_ES: R8.1, U5.7 (E/S)
/output_buffer/OPA548_ILIM: C14.1, R7.1, U5.3 (ILIM)
/output_buffer/VO_RAW: C19.1, R9.1, R38.1, U5.6 (OUT)
/output_buffer/VO_SNUB: C49.1, R38.2
AGND: C15.2, C16.2, C17.2 (-), C18.1 (+), C49.2; also elsewhere on the board

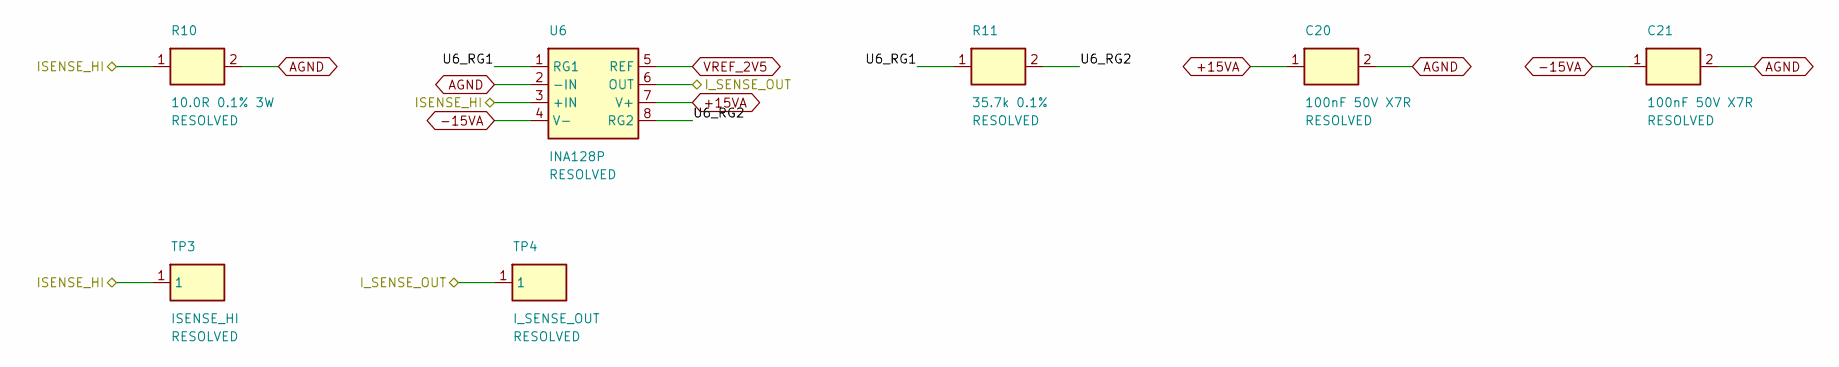
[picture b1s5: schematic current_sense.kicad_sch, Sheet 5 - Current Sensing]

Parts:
C20, C21: 100nF 50V X7R; C_0603_1608Metric; MPN generic
R10: 10.0R 0.1% 3W; R_Axial_DIN0614_L14.3mm_D5.7mm_P20.32mm_Horizontal; MPN RS02B10R00BE12
R11: 35.7k 0.1%; R_0603_1608Metric; MPN generic
TP3: ISENSE_HI; TestPoint_Pad_D1.5mm; MPN n/a
TP4: I_SENSE_OUT; TestPoint_Pad_D1.5mm; MPN n/a
U6: INA128P; DIP-8_W7.62mm; MPN INA128P

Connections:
+15VA: C20.1, U6.7 (V+); also elsewhere on the board
-15VA: C21.1, U6.4 (V-); also elsewhere on the board
/ISENSE_HI: R10.1, TP3.1, U6.3 (+IN); also elsewhere on the board
/I_SENSE_OUT: TP4.1, U6.6 (OUT); also elsewhere on the board
/current_sense/U6_RG1: R11.1, U6.1 (RG1)
/current_sense/U6_RG2: R11.2, U6.8 (RG2)
AGND: C20.2, C21.2, R10.2, U6.2 (-IN); also elsewhere on the board
VREF_2V5: U6.5 (REF); also elsewhere on the board

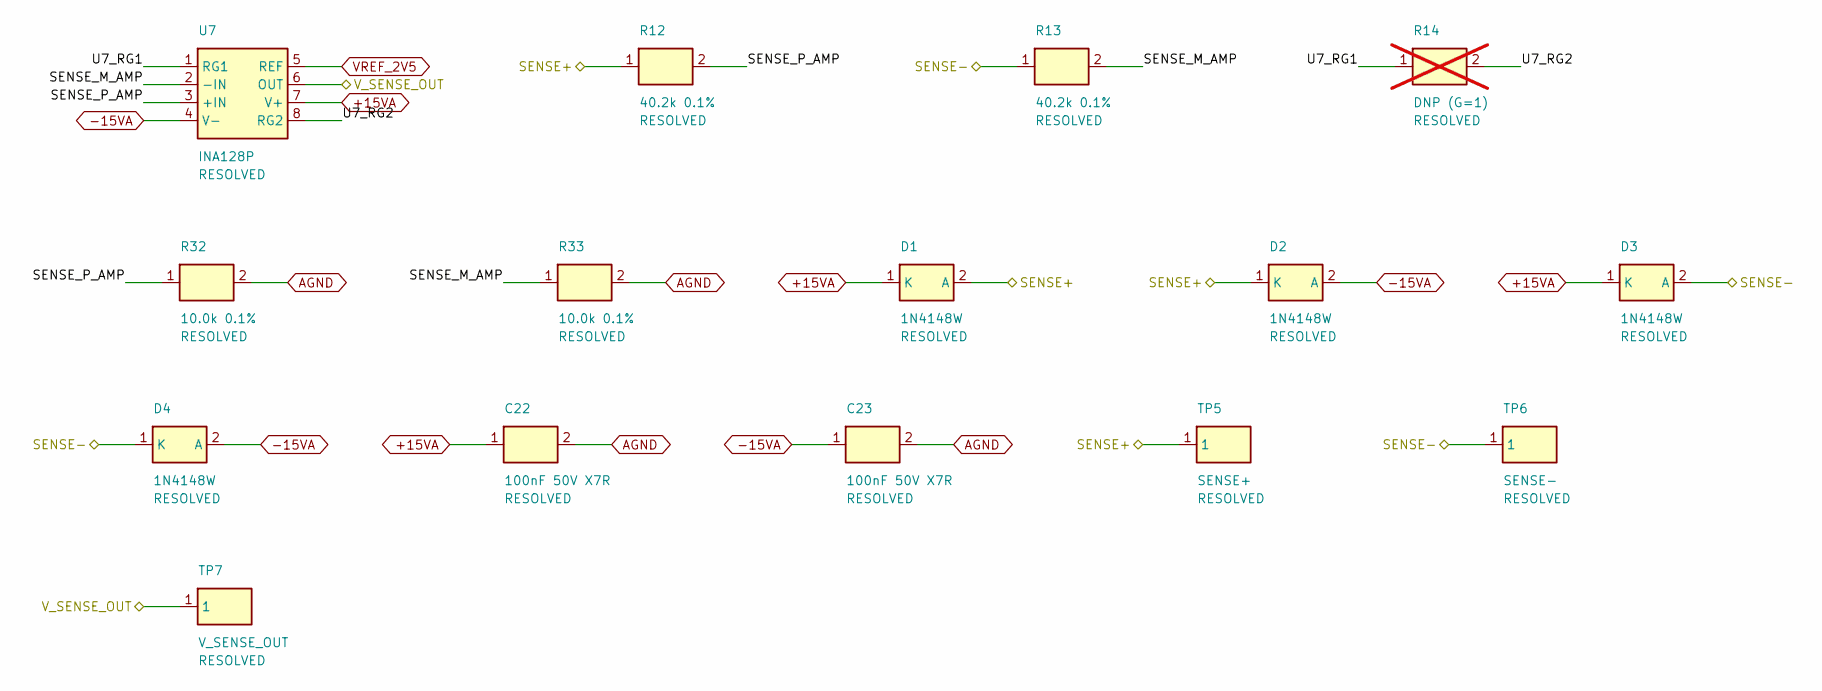
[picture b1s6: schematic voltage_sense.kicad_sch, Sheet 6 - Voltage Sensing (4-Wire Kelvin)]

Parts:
C22, C23: 100nF 50V X7R; C_0603_1608Metric; MPN generic
D1, D2, D3, D4: 1N4148W; D_SOD-123; MPN 1N4148W
R12, R13: 40.2k 0.1%; R_0603_1608Metric; MPN generic
R14: DNP (G=1); R_0603_1608Metric; MPN generic; not fitted
R32, R33: 10.0k 0.1%; R_0603_1608Metric; MPN generic
TP5: SENSE+; TestPoint_Pad_D1.5mm; MPN n/a
TP6: SENSE-; TestPoint_Pad_D1.5mm; MPN n/a
TP7: V_SENSE_OUT; TestPoint_Pad_D1.5mm; MPN n/a
U7: INA128P; DIP-8_W7.62mm; MPN INA128P

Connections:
+15VA: C22.1, D1.1 (K), D3.1 (K), U7.7 (V+); also elsewhere on the board
-15VA: C23.1, D2.2 (A), D4.2 (A), U7.4 (V-); also elsewhere on the board
/SENSE+: D1.2 (A), D2.1 (K), R12.1, TP5.1; also elsewhere on the board
/SENSE-: D3.2 (A), D4.1 (K), R13.1, TP6.1; also elsewhere on the board
/V_SENSE_OUT: TP7.1, U7.6 (OUT); also elsewhere on the board
/voltage_sense/SENSE_M_AMP: R13.2, R33.1, U7.2 (-IN)
/voltage_sense/SENSE_P_AMP: R12.2, R32.1, U7.3 (+IN)
/voltage_sense/U7_RG1: R14.1, U7.1 (RG1)
/voltage_sense/U7_RG2: R14.2, U7.8 (RG2)
AGND: C22.2, C23.2, R32.2, R33.2; also elsewhere on the board
VREF_2V5: U7.5 (REF); also elsewhere on the board

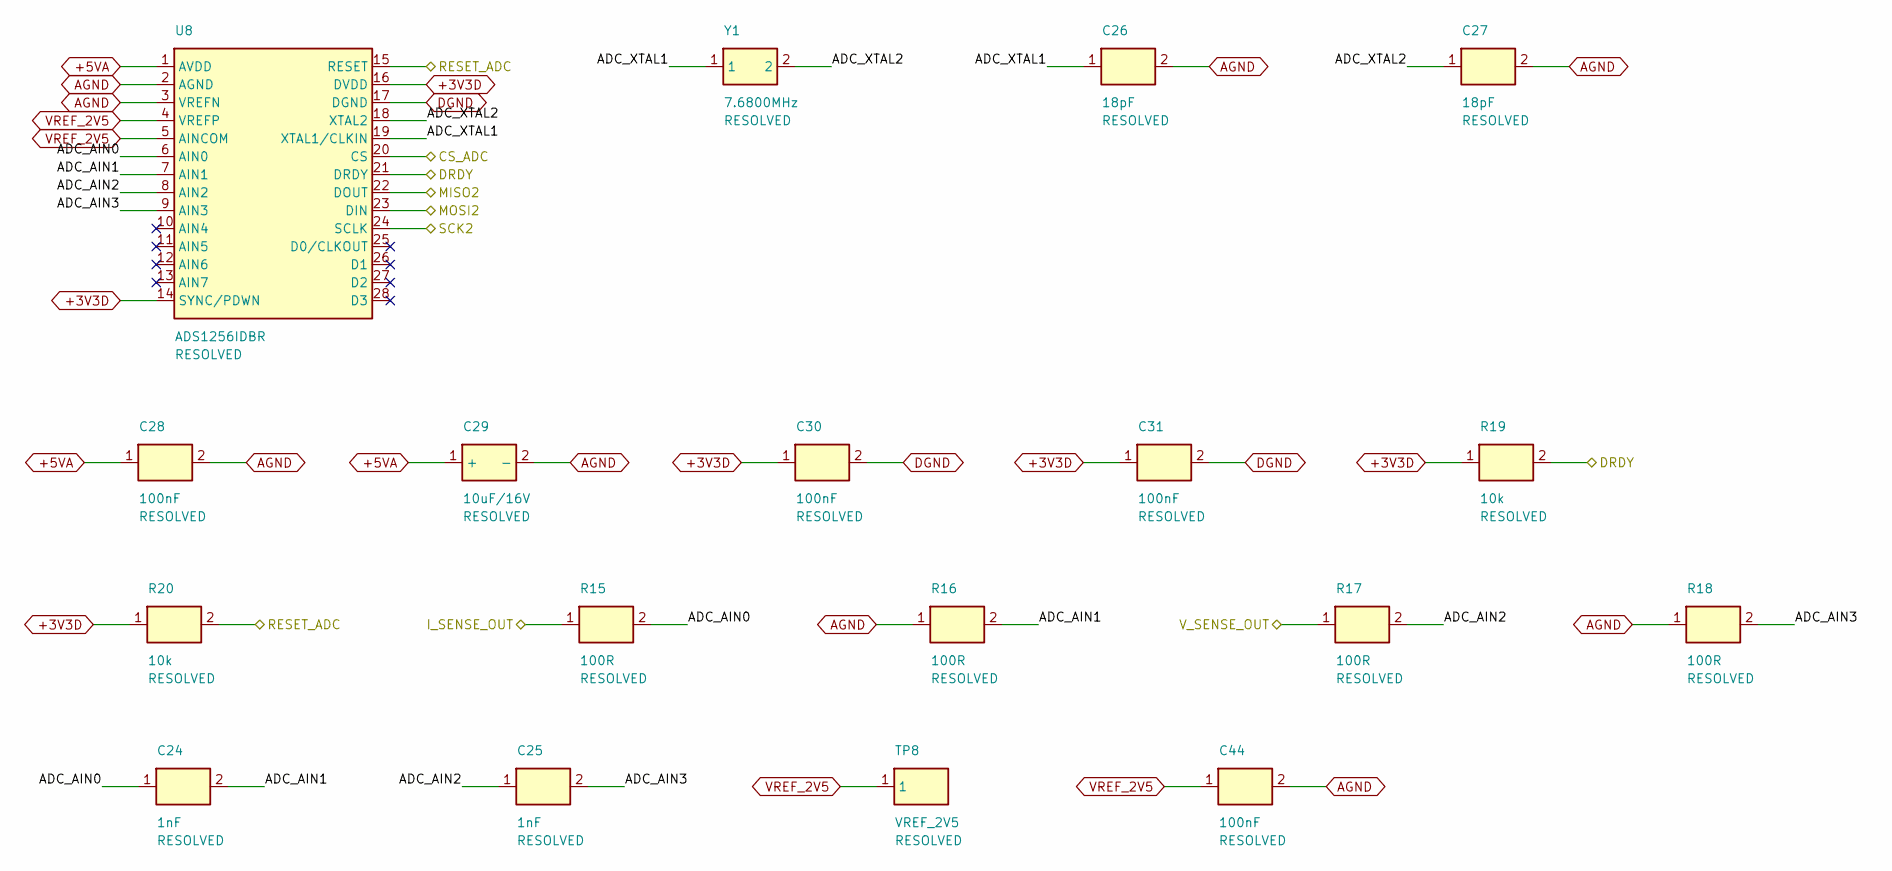
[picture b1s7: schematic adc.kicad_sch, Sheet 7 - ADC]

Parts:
C24, C25: 1nF; C_0603_1608Metric; MPN generic
C26, C27: 18pF; C_0603_1608Metric; MPN generic
C28, C30, C31, C44: 100nF; C_0603_1608Metric; MPN generic
C29: 10uF/16V; CP_EIA-3528-21_Kemet-B; MPN generic
R15, R16, R17, R18: 100R; R_0603_1608Metric; MPN generic
R19, R20: 10k; R_0603_1608Metric; MPN generic
TP8: VREF_2V5; TestPoint_Pad_D1.5mm; MPN n/a
U8: ADS1256IDBR; SSOP-28_5.3x10.2mm_P0.65mm; MPN ADS1256IDBR
Y1: 7.6800MHz; Crystal_SMD_HC49-SD; MPN generic

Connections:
+3V3D: C30.1, C31.1, R19.1, R20.1, U8.14 (SYNC/PDWN), U8.16 (DVDD); also elsewhere on the board
+5VA: C28.1, C29.1 (+), U8.1 (AVDD); also elsewhere on the board
/CS_ADC: U8.20 (CS); also elsewhere on the board
/DRDY: R19.2, U8.21 (DRDY); also elsewhere on the board
/I_SENSE_OUT: R15.1; also elsewhere on the board
/MISO2: U8.22 (DOUT); also elsewhere on the board
/MOSI2: U8.23 (DIN); also elsewhere on the board
/RESET_ADC: R20.2, U8.15 (RESET); also elsewhere on the board
/SCK2: U8.24 (SCLK); also elsewhere on the board
/V_SENSE_OUT: R17.1; also elsewhere on the board
/adc/ADC_AIN0: C24.1, R15.2, U8.6 (AIN0)
/adc/ADC_AIN1: C24.2, R16.2, U8.7 (AIN1)
/adc/ADC_AIN2: C25.1, R17.2, U8.8 (AIN2)
/adc/ADC_AIN3: C25.2, R18.2, U8.9 (AIN3)
/adc/ADC_XTAL1: C26.1, U8.19 (XTAL1/CLKIN), Y1.1
/adc/ADC_XTAL2: C27.1, U8.18 (XTAL2), Y1.2
AGND: C26.2, C27.2, C28.2, C29.2 (-), C44.2, R16.1, R18.1, U8.2 (AGND), U8.3 (VREFN); also elsewhere on the board
DGND: C30.2, C31.2, U8.17 (DGND); also elsewhere on the board
VREF_2V5: C44.1, TP8.1, U8.4 (VREFP), U8.5 (AINCOM); also elsewhere on the board
